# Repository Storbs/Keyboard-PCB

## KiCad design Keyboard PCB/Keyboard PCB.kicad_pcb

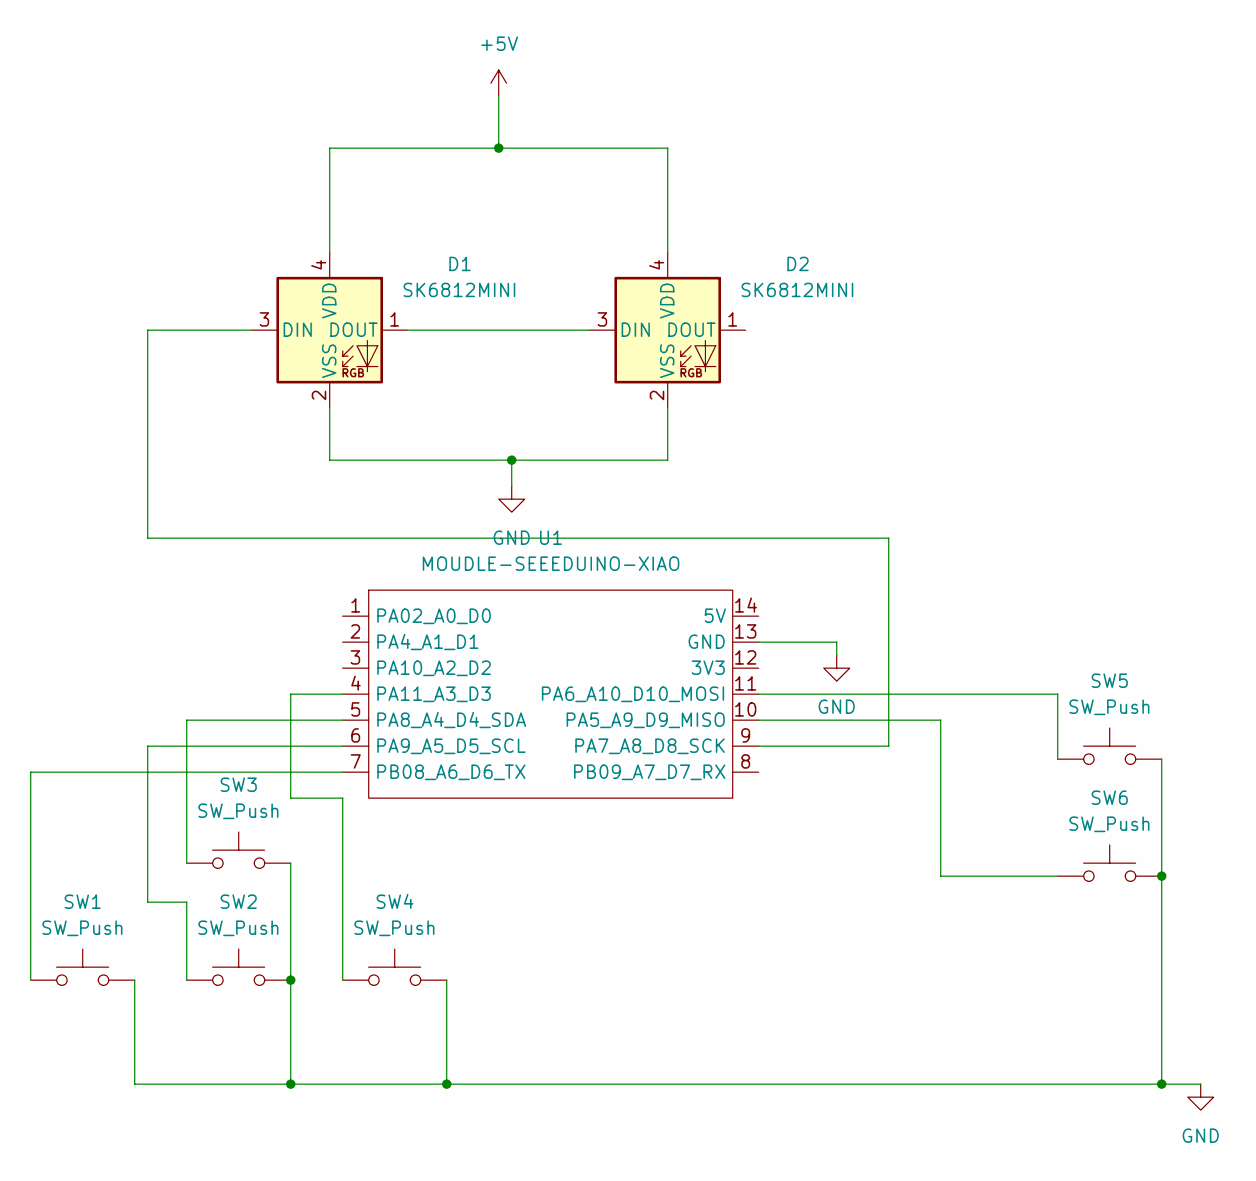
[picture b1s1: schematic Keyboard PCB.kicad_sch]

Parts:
D1, D2: SK6812MINI; LED_SK6812MINI_PLCC4_3.5x3.5mm_P1.75mm
SW1, SW2, SW3, SW4, SW5, SW6: SW_Push; SW_Cherry_MX_1.00u_PCB
U1: MOUDLE-SEEEDUINO-XIAO; XIAO-Generic-Hybrid-14P-2.54-21X17.8MM

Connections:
+5V: D1.4 (VDD), D2.4 (VDD)
GND: D1.2 (VSS), D2.2 (VSS), SW1.2, SW2.2, SW3.2, SW4.2, SW5.2, SW6.2, U1.13 (GND)
unnamed: D1.3 (DIN), U1.9 (PA7_A8_D8_SCK)
unnamed: D1.1 (DOUT), D2.3 (DIN)
unnamed: SW6.1, U1.10 (PA5_A9_D9_MISO)
unnamed: SW5.1, U1.11 (PA6_A10_D10_MOSI)
unnamed: SW3.1, U1.5 (PA8_A4_D4_SDA)
unnamed: SW2.1, U1.6 (PA9_A5_D5_SCL)
unnamed: SW4.1, U1.4 (PA11_A3_D3)
unnamed: SW1.1, U1.7 (PB08_A6_D6_TX)

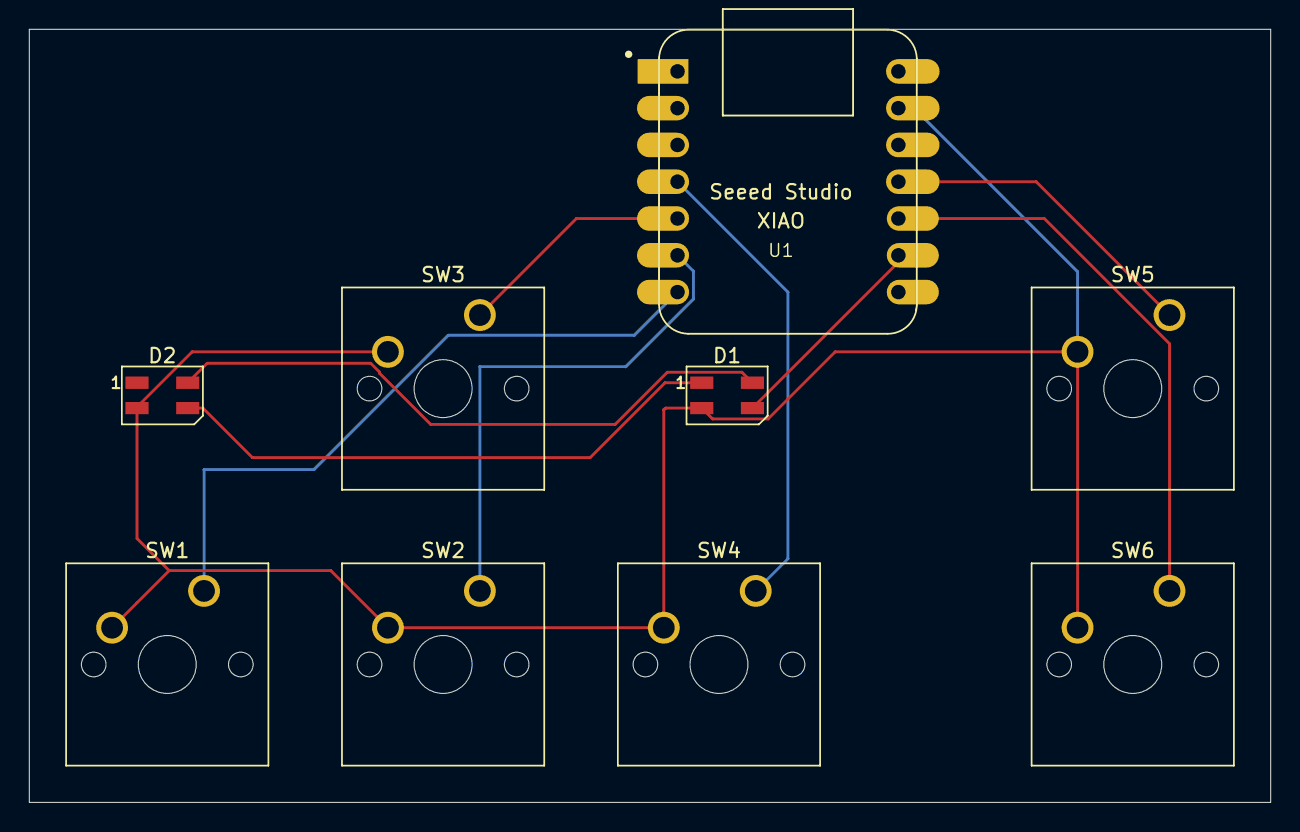
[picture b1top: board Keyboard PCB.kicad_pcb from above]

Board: 2 copper layers, 85.7 x 53.4 mm, 9 parts (0 on the bottom side), 10 nets.

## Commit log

2026-03-20 Created the KiCAD file
2026-03-20 Made the Schematic
2026-03-20 PCB (first revision)
2026-03-20 Updated PCB
2026-03-20 Who needs autosaves?
2026-03-21 Honestly not sure what I did
2026-03-21 Adjusted wiring
    I flipped the XIAO microcontroller because I was worried it would mess up the build process if it was on the bottom. For some reason the tutorial says to put it on the back side but most people just 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
2026-03-22 Saved the Kicad files
